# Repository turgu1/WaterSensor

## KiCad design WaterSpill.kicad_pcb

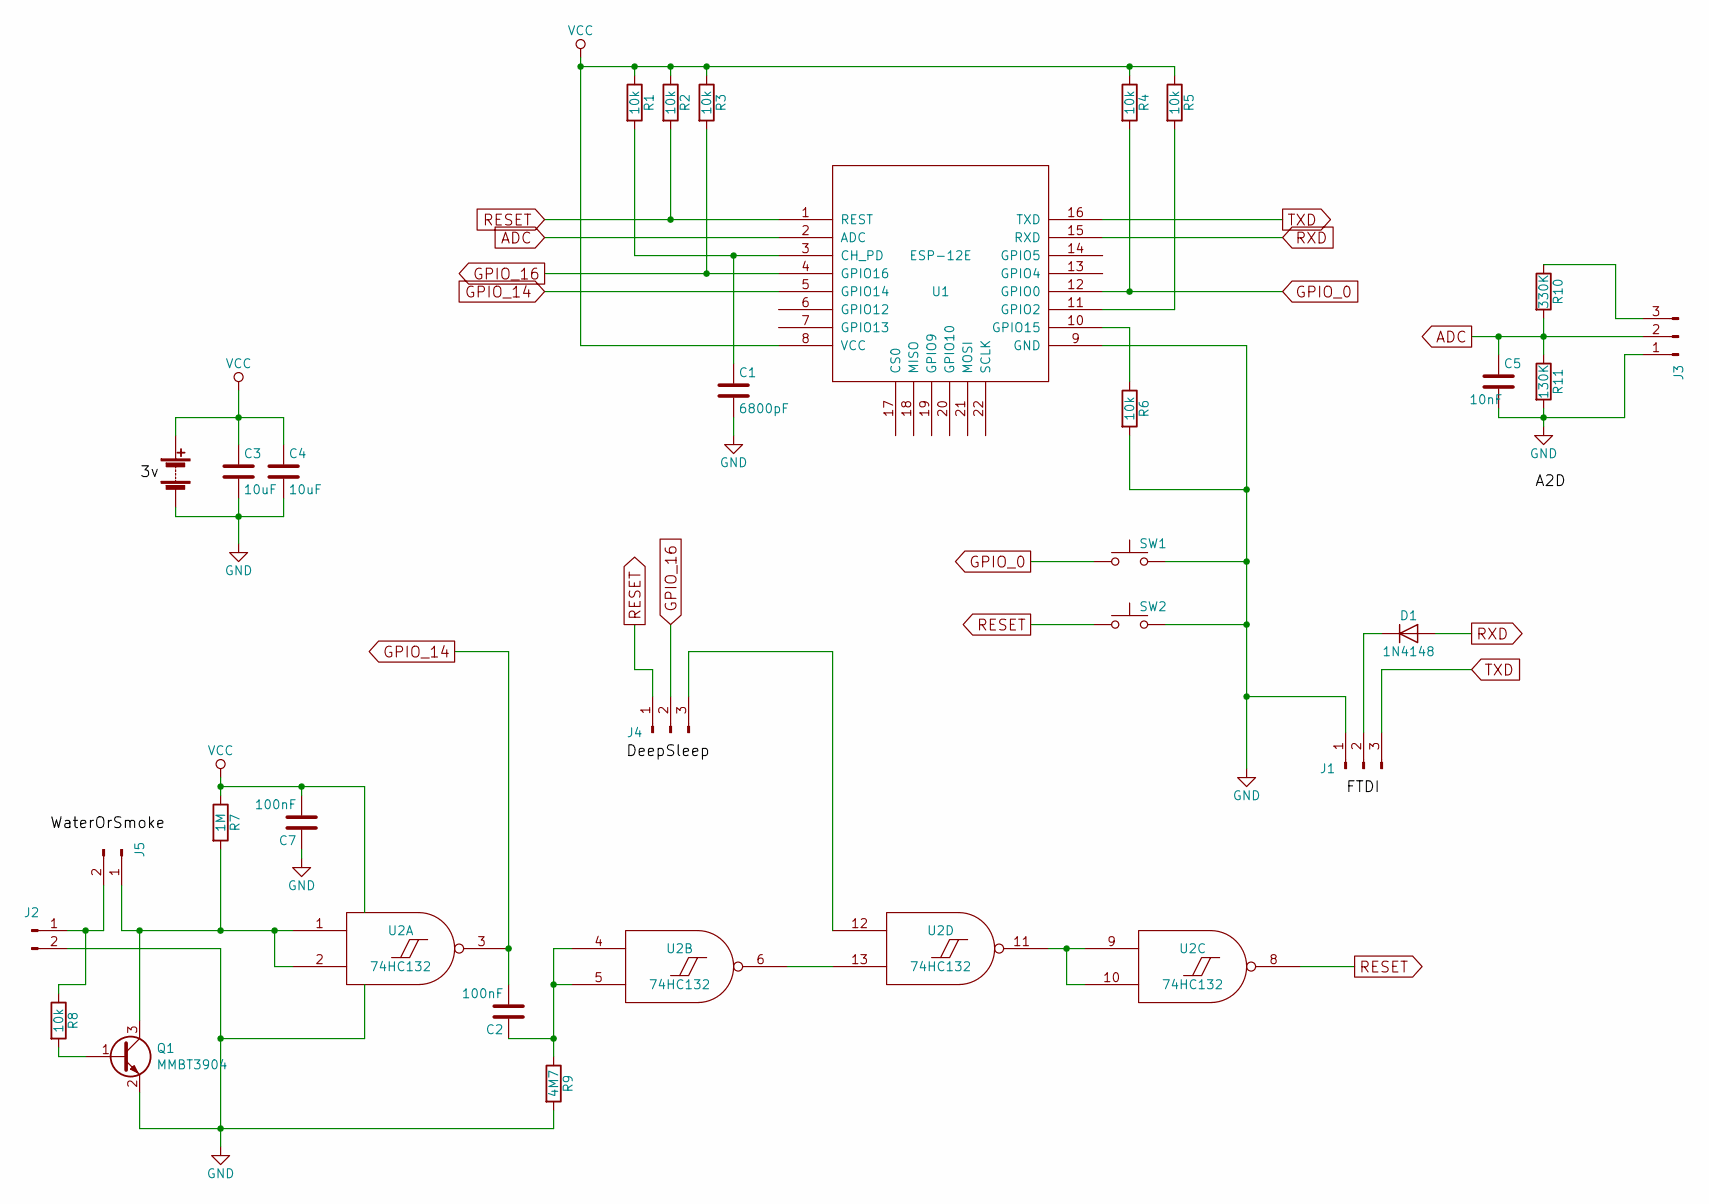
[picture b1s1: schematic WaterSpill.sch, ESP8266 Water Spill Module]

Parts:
BT1: Battery; Pin_Header_Straight_1x02_Pitch2.54mm
C1: 6800pF; C_0805_HandSoldering
C2, C7: 100nF; C_0805_HandSoldering
C3, C4: 10uF; C_0805_HandSoldering
C5: 10nF; C_0805_HandSoldering
D1: 1N4148; D_SOD-323_HandSoldering
J1, J3, J4: Conn_01x03_Male; Pin_Header_Straight_1x03_Pitch2.54mm
J2, J5: Conn_01x02_Male; Pin_Header_Straight_1x02_Pitch2.54mm
Q1: MMBT3904; SOT-23
R1, R2, R3, R4, R5, R6, R8: 10k; R_0805_HandSoldering
R7: 1M; R_0805_HandSoldering
R9: 4M7; R_0805_HandSoldering
R10: 330K; R_0805_HandSoldering
R11: 130K; R_0805_HandSoldering
SW1, SW2: SW_Push; SW_SPST_FSMSM
U1: ESP-12E; ESP-12E_SMD
U2: 74HC132; SOIC-14_3.9x8.7mm_Pitch1.27mm

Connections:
ADC: C5.1, J3.2, R10.2, R11.1, U1.2 (ADC)
GND: BT1.2 (-), C1.2, C3.2, C4.2, C5.2, C7.1, J1.1, J2.2, J3.1, Q1.2 (E), R6.2, R9.2, R11.2, SW1.2, SW2.2, U1.9 (GND), U2.7 (GND)
GPIO_0: R4.2, SW1.1, U1.12 (GPIO0)
GPIO_14: C2.2, U1.5 (GPIO14), U2.3
GPIO_16: J4.2, R3.2, U1.4 (GPIO16)
unnamed: C1.1, R1.2, U1.3 (CH_PD)
unnamed: C2.1, R9.1, U2.4, U2.5
unnamed: D1.1 (K), J1.2
unnamed: J2.1, J5.2, R8.1
unnamed: J3.3, R10.1
unnamed: J4.3, U2.12
unnamed: J5.1, Q1.3 (C), R7.2, U2.1, U2.2
unnamed: Q1.1 (B), R8.2
unnamed: R5.2, U1.11 (GPIO2)
unnamed: R6.1, U1.10 (GPIO15)
unnamed: U2.9, U2.10, U2.11
unnamed: U2.6, U2.13
RESET: J4.1, R2.2, SW2.1, U1.1 (REST), U2.8
RXD: D1.2 (A), U1.15 (RXD)
TXD: J1.3, U1.16 (TXD)
VCC: BT1.1 (+), C3.1, C4.1, C7.2, R1.1, R2.1, R3.1, R4.1, R5.1, R7.1, U1.8 (VCC), U2.14 (VCC)

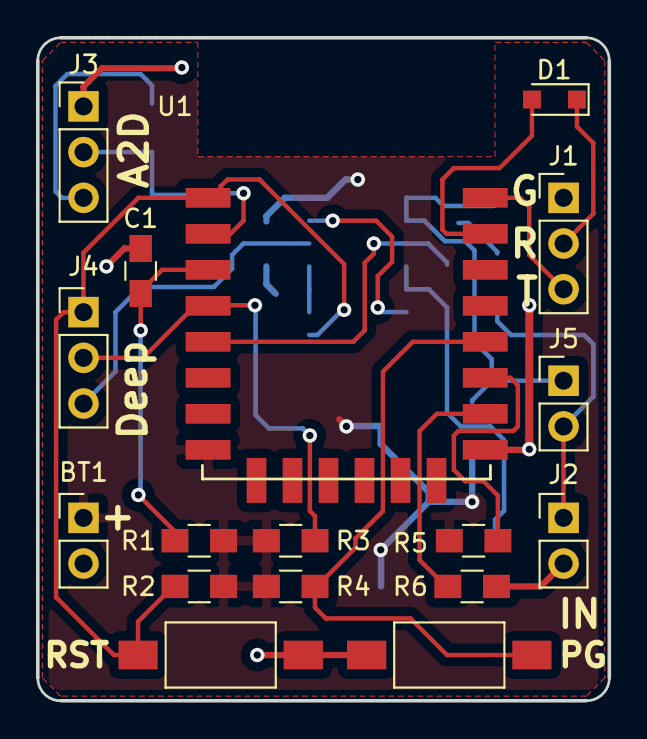
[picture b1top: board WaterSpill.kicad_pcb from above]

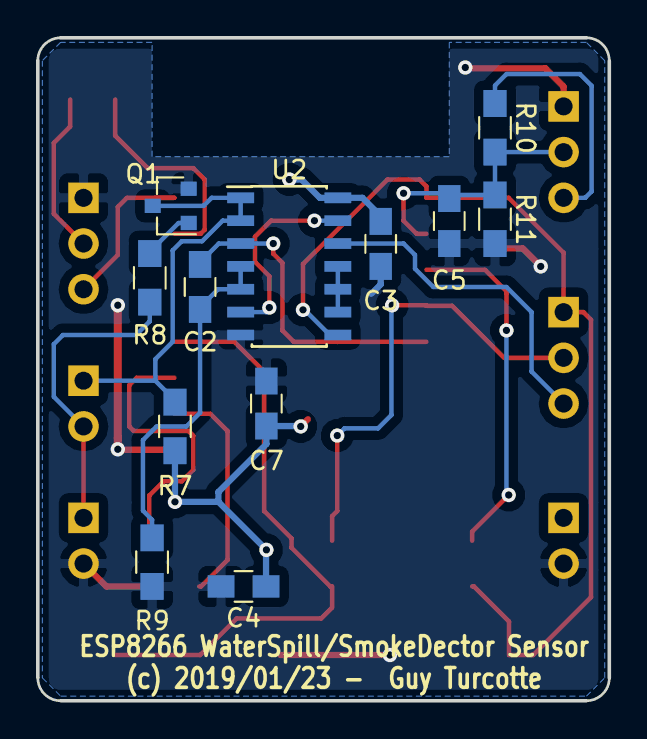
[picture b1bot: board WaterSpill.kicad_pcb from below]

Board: 2 copper layers, 31.7 x 36.8 mm, 29 parts (12 on the bottom side), 21 nets.

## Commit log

2019-01-23 Added Smoke Sensor support
2019-01-23 Silk Screen text added
2019-01-24 Corrected transistor footprint
2019-01-24 Added Gerber files for etching

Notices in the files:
WaterSpill.kicad_pcb:
(c) 2019/01/23 -  Guy Turcotte
